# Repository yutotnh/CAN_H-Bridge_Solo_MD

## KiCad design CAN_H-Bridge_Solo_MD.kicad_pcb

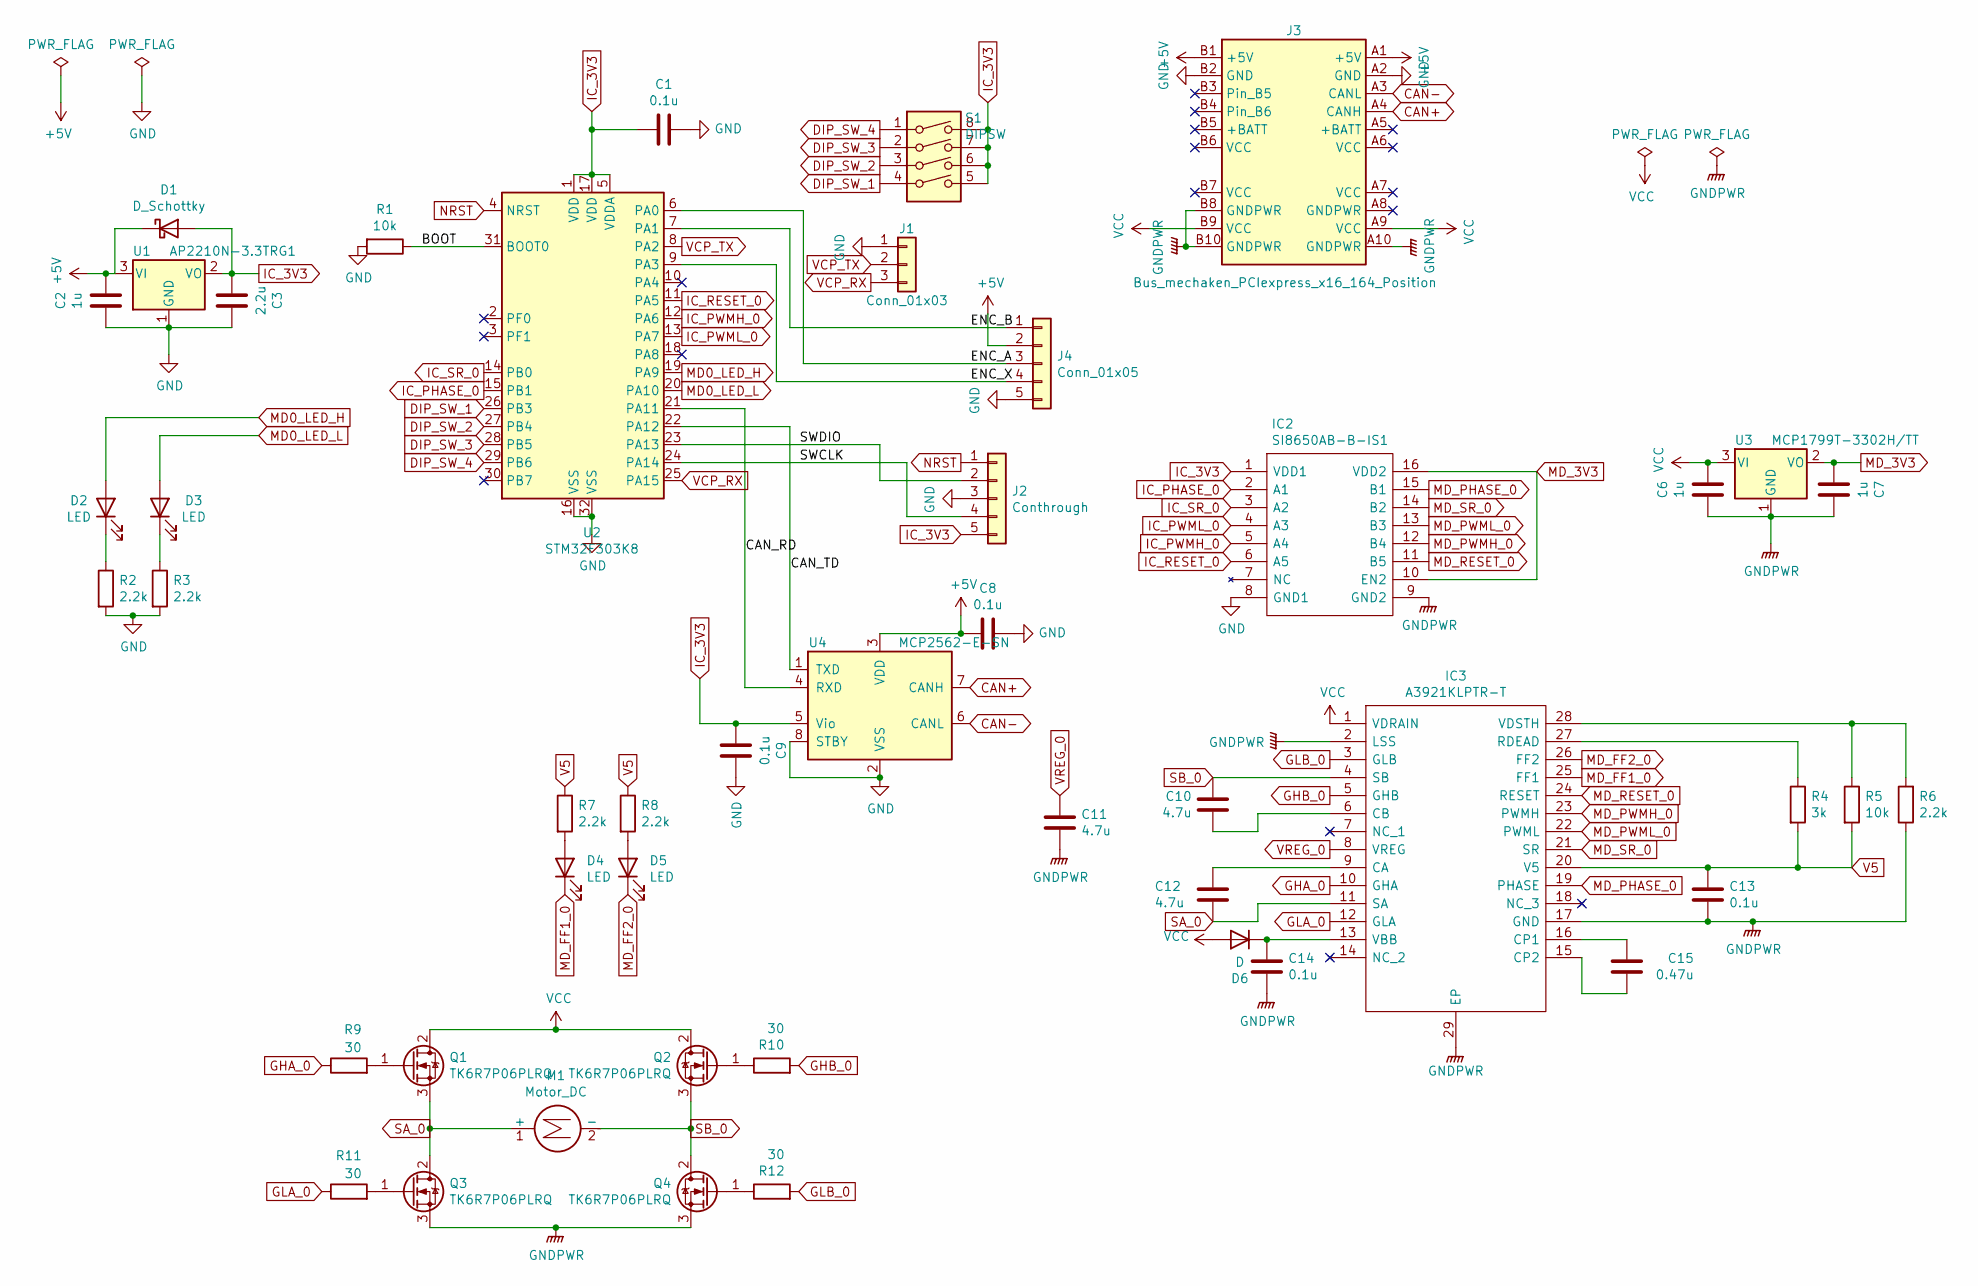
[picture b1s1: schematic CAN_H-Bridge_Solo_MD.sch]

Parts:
C1, C8, C9, C13, C14: 0.1u; C_0805_2012Metric_Pad1.15x1.40mm_HandSolder
C2, C6, C7: 1u; C_0805_2012Metric_Pad1.15x1.40mm_HandSolder
C3: 2.2u; C_0805_2012Metric_Pad1.15x1.40mm_HandSolder
C10, C11, C12: 4.7u; C_0805_2012Metric_Pad1.15x1.40mm_HandSolder
C15: 0.47u; C_0805_2012Metric_Pad1.15x1.40mm_HandSolder
D1: D_Schottky; D_0603_1608Metric_Pad1.05x0.95mm_HandSolder
D2, D3, D4, D5: LED; LED_0603_1608Metric_Castellated
D6: D; D_0603_1608Metric_Pad1.05x0.95mm_HandSolder
IC2: SI8650AB-B-IS1; SOIC-16_3.9x9.9mm_P1.27mm; Mouser Part Number 634-SI8650AB-B-IS1
IC3: A3921KLPTR-T; SOP65P640X120-29N; Manufacturer_Part_Number A3921KLPTR-T
J1: Conn_01x03; PinHeader_1x03_P2.54mm_Vertical
J2: Conthrough; PinHeader_1x05_P2.54mm_Vertical
J3: Bus_mechaken_PCIexpress_x16_164_Position; BUS_mechaken_PCIexpress_x16
J4: Conn_01x05; PinHeader_1x05_P2.54mm_Vertical
M1: Motor_DC; XT60PW
Q1, Q2, Q3, Q4: TK6R7P06PLRQ; TO-252-2
R1, R5: 10k; R_0603_1608Metric_Pad1.05x0.95mm_HandSolder
R2, R3, R6, R7, R8: 2.2k; R_0603_1608Metric_Pad1.05x0.95mm_HandSolder
R4: 3k; R_0603_1608Metric_Pad1.05x0.95mm_HandSolder
R9, R10, R11, R12: 30; R_0603_1608Metric_Pad1.05x0.95mm_HandSolder
S1: DIPSW; DIP-8_W7.62mm; Manufacturer_Part_Number IKD0403101
U1: AP2210N-3.3TRG1; SOT-23W_Handsoldering
U2: STM32F303K8; LQFP-32_7x7mm_P0.8mm
U3: MCP1799T-3302H/TT; SOT-23_Handsoldering
U4: MCP2562-E-SN; SOIC-8_3.9x4.9mm_P1.27mm

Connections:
+5V: C2.1, C8.2, D1.1 (K), J3.A1 (+5V), J3.B1 (+5V), J4.2, U1.3 (VI), U4.3 (VDD)
/BOOT: R1.1, U2.31 (BOOT0)
/CAN_RD: U2.21 (PA11), U4.4 (RXD)
/CAN_TD: U2.22 (PA12), U4.1 (TXD)
/ENC_A: J4.3, U2.6 (PA0)
/ENC_B: J4.1, U2.7 (PA1)
/ENC_X: J4.4, U2.9 (PA3)
/SWCLK: J2.4, U2.24 (PA14)
/SWDIO: J2.2, U2.23 (PA13)
CAN+: J3.A4 (CANH), U4.7 (CANH)
CAN-: J3.A3 (CANL), U4.6 (CANL)
DIP_SW_1: S1.4, U2.26 (PB3)
DIP_SW_2: S1.3, U2.27 (PB4)
DIP_SW_3: S1.2, U2.28 (PB5)
DIP_SW_4: S1.1, U2.29 (PB6)
GHA_0: IC3.10 (GHA), R9.1
GHB_0: IC3.5 (GHB), R10.2
GLA_0: IC3.12 (GLA), R11.1
GLB_0: IC3.3 (GLB), R12.2
GND: C1.1, C2.2, C3.1, C8.1, C9.1, IC2.8 (GND1), J1.1, J2.3, J3.A2 (GND), J3.B2 (GND), J4.5, R1.2, R2.2, R3.2, U1.1 (GND), U2.16 (VSS), U2.32 (VSS), U4.2 (VSS), U4.8 (STBY)
GNDPWR: C6.2, C7.1, C11.2, C13.2, C14.2, IC2.9 (GND2), IC3.2 (LSS), IC3.17 (GND), IC3.29 (EP), J3.A10 (GNDPWR), J3.B8 (GNDPWR), J3.B10 (GNDPWR), Q3.3 (S), Q4.3 (S), R6.1, U3.1 (GND)
IC_3V3: C1.2, C3.2, C9.2, D1.2 (A), IC2.1 (VDD1), J2.5, S1.5, S1.6, S1.7, S1.8, U1.2 (VO), U2.1 (VDD), U2.5 (VDDA), U2.17 (VDD), U4.5 (Vio)
IC_PHASE_0: IC2.2 (A1), U2.15 (PB1)
IC_PWMH_0: IC2.5 (A4), U2.12 (PA6)
IC_PWML_0: IC2.4 (A3), U2.13 (PA7)
IC_RESET_0: IC2.6 (A5), U2.11 (PA5)
IC_SR_0: IC2.3 (A2), U2.14 (PB0)
MD0_LED_H: D2.2 (A), U2.19 (PA9)
MD0_LED_L: D3.2 (A), U2.20 (PA10)
MD_3V3: C7.2, IC2.10 (EN2), IC2.16 (VDD2), U3.2 (VO)
MD_FF1_0: D4.1 (K), IC3.25 (FF1)
MD_FF2_0: D5.1 (K), IC3.26 (FF2)
MD_PHASE_0: IC2.15 (B1), IC3.19 (PHASE)
MD_PWMH_0: IC2.12 (B4), IC3.23 (PWMH)
MD_PWML_0: IC2.13 (B3), IC3.22 (PWML)
MD_RESET_0: IC2.11 (B5), IC3.24 (RESET)
MD_SR_0: IC2.14 (B2), IC3.21 (SR)
NRST: J2.1, U2.4 (NRST)
unnamed: C10.1, IC3.6 (CB)
unnamed: C12.1, IC3.9 (CA)
unnamed: C14.1, D6.1 (K), IC3.13 (VBB)
unnamed: C15.1, IC3.15 (CP2)
unnamed: C15.2, IC3.16 (CP1)
unnamed: D2.1 (K), R2.1
unnamed: D3.1 (K), R3.1
unnamed: D4.2 (A), R7.2
unnamed: D5.2 (A), R8.2
unnamed: IC3.27 (RDEAD), R4.1
unnamed: IC3.28 (VDSTH), R5.1, R6.2
unnamed: Q1.1 (G), R9.2
unnamed: Q2.1 (G), R10.1
unnamed: Q3.1 (G), R11.2
unnamed: Q4.1 (G), R12.1
SA_0: C12.2, IC3.11 (SA), M1.1 (+), Q1.3 (S), Q3.2 (D)
SB_0: C10.2, IC3.4 (SB), M1.2 (-), Q2.3 (S), Q4.2 (D)
V5: C13.1, IC3.20 (V5), R4.2, R5.2, R7.1, R8.1
VCC: C6.1, D6.2 (A), IC3.1 (VDRAIN), J3.A9 (VCC), J3.B9 (VCC), Q1.2 (D), Q2.2 (D), U3.3 (VI)
VCP_RX: J1.3, U2.25 (PA15)
VCP_TX: J1.2, U2.8 (PA2)
VREG_0: C11.1, IC3.8 (VREG)

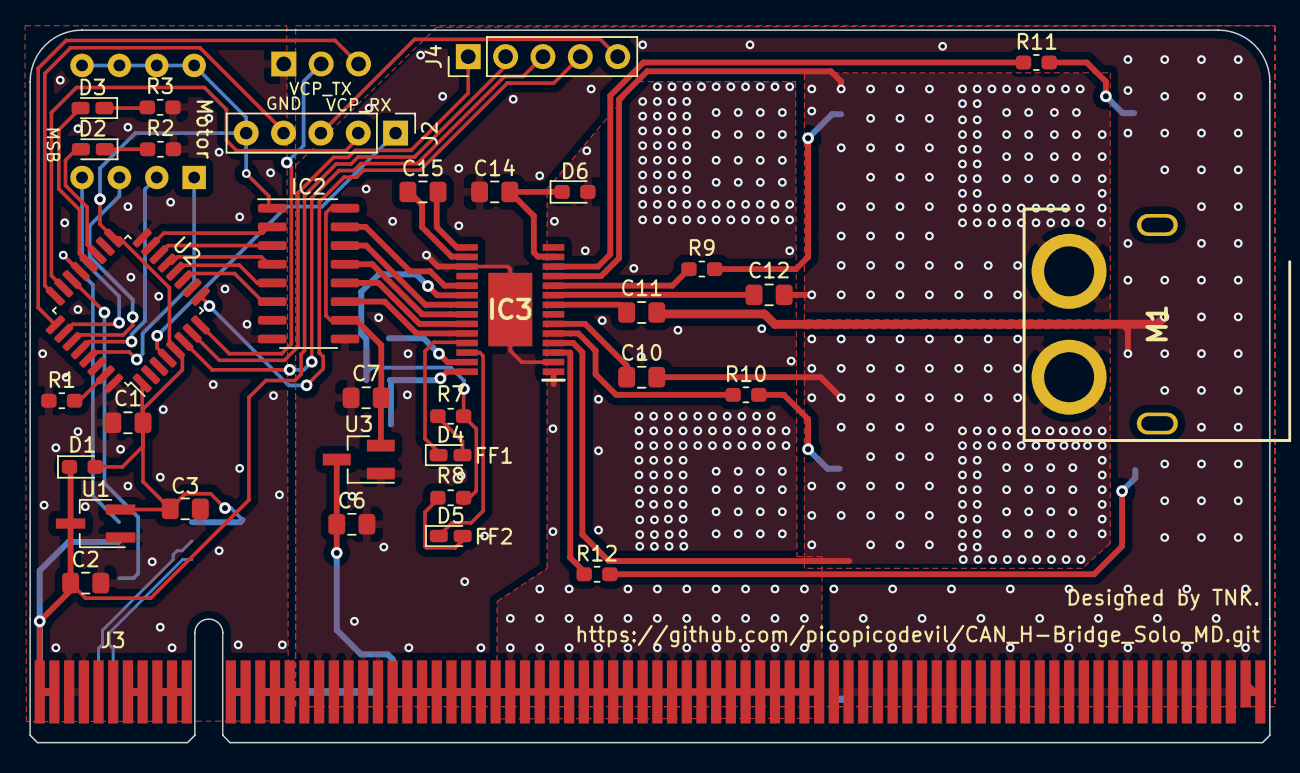
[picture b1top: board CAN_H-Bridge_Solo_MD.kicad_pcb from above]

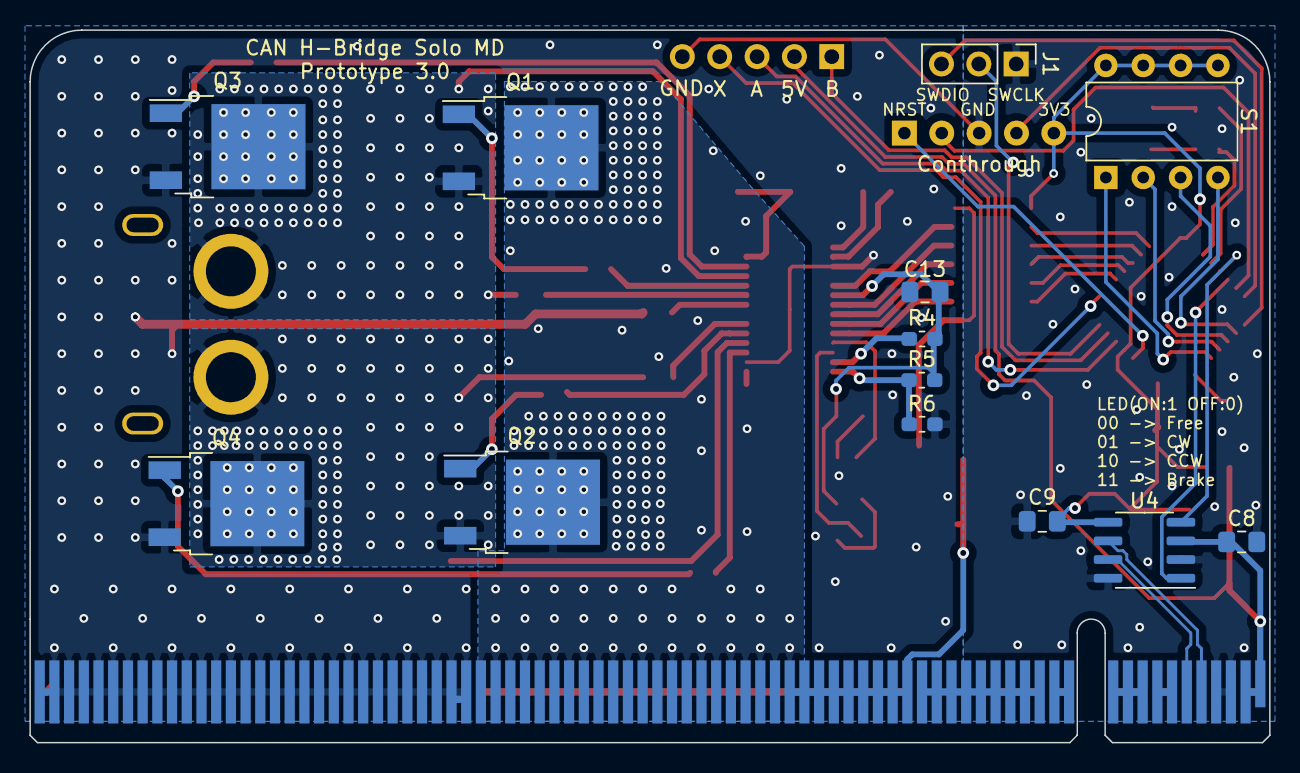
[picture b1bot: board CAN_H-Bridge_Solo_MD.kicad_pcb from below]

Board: 2 copper layers, 84.3 x 48.4 mm, 47 parts (13 on the bottom side), 60 nets.

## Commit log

2019-12-27 Prototype-1.0
2020-01-24 change
    FETのドレイン端子を移動
    パッドを手はんだ用に変更
    PCIeコネクタを変更
2020-01-26 change
    レギュレータを新規に追加
    その他細かな修正
2020-01-29 clean
2020-02-02 release
2020-02-02 create
2020-02-10 clean
    LEDの配線を変更
    PA9 <-> PA10
2020-02-21 add
    LDOの逆電圧防止用にSBDを追加
2020-06-18 change
    反転前
2020-06-18 change
    FET反転
2020-06-18 change
    モーターの許容電流を増加
2020-06-19 change
    ビアなどの増加
2020-06-21 Release
    Release Prototype-2.0
2020-06-21 add
    gitignoreを追加
2020-06-21 .gitignore is now working
2021-02-14 Update: エンコーダ対応
2021-02-14 Update: 配線の修正
2021-02-14 Update: シルク配置を上側に変更
2021-09-24 Update: MCUをF042K6からF303K8へ変更
